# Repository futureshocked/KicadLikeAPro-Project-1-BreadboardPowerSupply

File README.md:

View this project on [CADLAB.io](https://cadlab.io/project/28684). 

# Kicad Like a Pro Project 1: A Breadboard Power Supply

This is the first project from the book and video course [Kicad Like a Pro](https://techexplorations.com/so/kicada/). It implements a simple breadboard power supply.

In this project, you will use all of Kicad’s main features that you learned about in Parts 2 and 3 of the book. Particularly, you will learn:

1.How to design a schematic of your board in Eeschema

2.How to design a layout for your board with externally-imposed physical restrictions

3.How to take measurements that relate to the board’s mechanical specifications and used them to design the board outline

4.How to apply the linear schematic design workflow in a real project

5.How to apply the linear layout design workflow in a real project

6.How to select symbols from the library, and associate them with footprints

7.How to manually route the board

8.How to manufacture the board using an online manufacturer

This repository contains multiple commits at each step of the design process, as Peter was going through it. 
Feel free to clone this repository on your computer and make any modifications you feel like.

This project is the first complete and realistic one in this book. 

You will learn to use Kicad’s most important functions, and experience a simplified version of the PCB design process. 

In this project, you will build a double-sided PCB for a 5V power supply. 

You will be able to use this power supply to power your breadboard Arduino projects, or any project that requires a 5V power 
supply. As an input to your power supply, you can use an old DC or AC walled power supply, as long as its output voltage does 
not exceed 35V.

In the process of designing your power supply, you will learn all the skills you need to create PCBs of comparable complexity.

You will not learn everything there is to know in Kicad; you will not suddenly become an experienced PCB designer. 

But, you will have the opportunity to apply the principles you learned in Part 3, and create a respectable board. 

Go to txplore.com for more information about this book and other Tech Explorations courses and projects.

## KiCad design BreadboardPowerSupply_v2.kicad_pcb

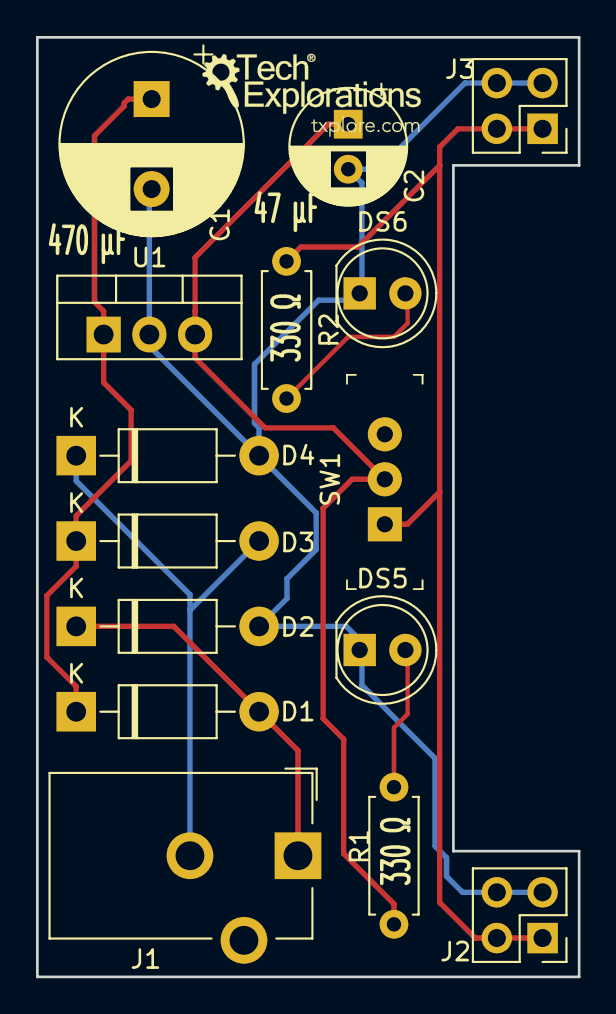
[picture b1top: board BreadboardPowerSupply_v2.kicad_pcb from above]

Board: 2 copper layers, 30.1 x 52.2 mm, 15 parts (0 on the bottom side), 8 nets.

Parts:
C1: CP; CP_Radial_D10.0mm_P5.00mm
C2: CP; CP_Radial_D6.3mm_P2.50mm
D1, D2, D3, D4: D; D_DO-41_SOD81_P10.16mm_Horizontal
DS5, DS6: LED; LED_D5.0mm
J1: Barrel_Jack_Switch; BarrelJack_CUI_PJ-102AH_Horizontal
J2, J3: Conn_02x02_Odd_Even; PinHeader_2x02_P2.54mm_Vertical
R1, R2: R; R_Axial_DIN0207_L6.3mm_D2.5mm_P7.62mm_Horizontal
SW1: SW_DPDT_x2; Switch_Slide_11.6x4mm_EG1218
U1: LM7805_TO220; TO-220-3_Vertical

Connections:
/V1: D1.2, D2.1, J1.1
/V2: D3.2, D4.1, J1.2
/V-: C1.2, C2.2, D2.2, D4.2, DS5.1, DS6.1, J2.3, J2.4, J3.3, J3.4, U1.2
/Vin: C1.1, D1.1, D3.1, U1.1
/Vout1: C2.1, R1.1, SW1.2, U1.3
/Vout2: J2.1, J2.2, J3.1, J3.2, R2.1, SW1.1
unnamed: DS5.2, R1.2
unnamed: DS6.2, R2.2

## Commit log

2018-08-13 First commit.
2018-08-13 Added text label.
2018-08-13 Added 2nd text label.
2018-08-13 Test 3
2018-08-13 Removed experimental text.
2018-08-13 Components annotated.
2018-08-14 Completed wiring, without nets.
2018-08-14 Added power flags.
2018-08-14 Added net labels.
2018-08-14 Completed ERC.
2018-08-14 Marked functional groups.
2018-08-14 Added descriptibe text, and finished with the schematic.
2018-08-15 Started layout in Pcbnew. Finished with design rules.
2018-08-15 Placement of footprints almost done. Fixed an incorrect association for C1.
2018-08-15 Placement completed.
2018-08-15 Added additional net names for power.
2018-08-16 Tracing is complete.
2018-08-16 Added silkscreen logos.
2018-08-16 Silkscreen completed.
2018-08-16 Done with last DRC.
2018-08-26 Added Gerber files.
2018-09-17 Replaced capacitor symbols as per IEC 60617 and IEEE 315, Clause 2.2.1 Style 1.
2018-09-17 Replaced designation of LEDs with DS as per IEEE 315, Clause 22.4
2018-09-17 Fixed various cosmetic issues with layout.
2018-09-17 Added non-class letter N for fenced-in areas.
2021-07-29 Backlink to CADLAB.io has been added.
